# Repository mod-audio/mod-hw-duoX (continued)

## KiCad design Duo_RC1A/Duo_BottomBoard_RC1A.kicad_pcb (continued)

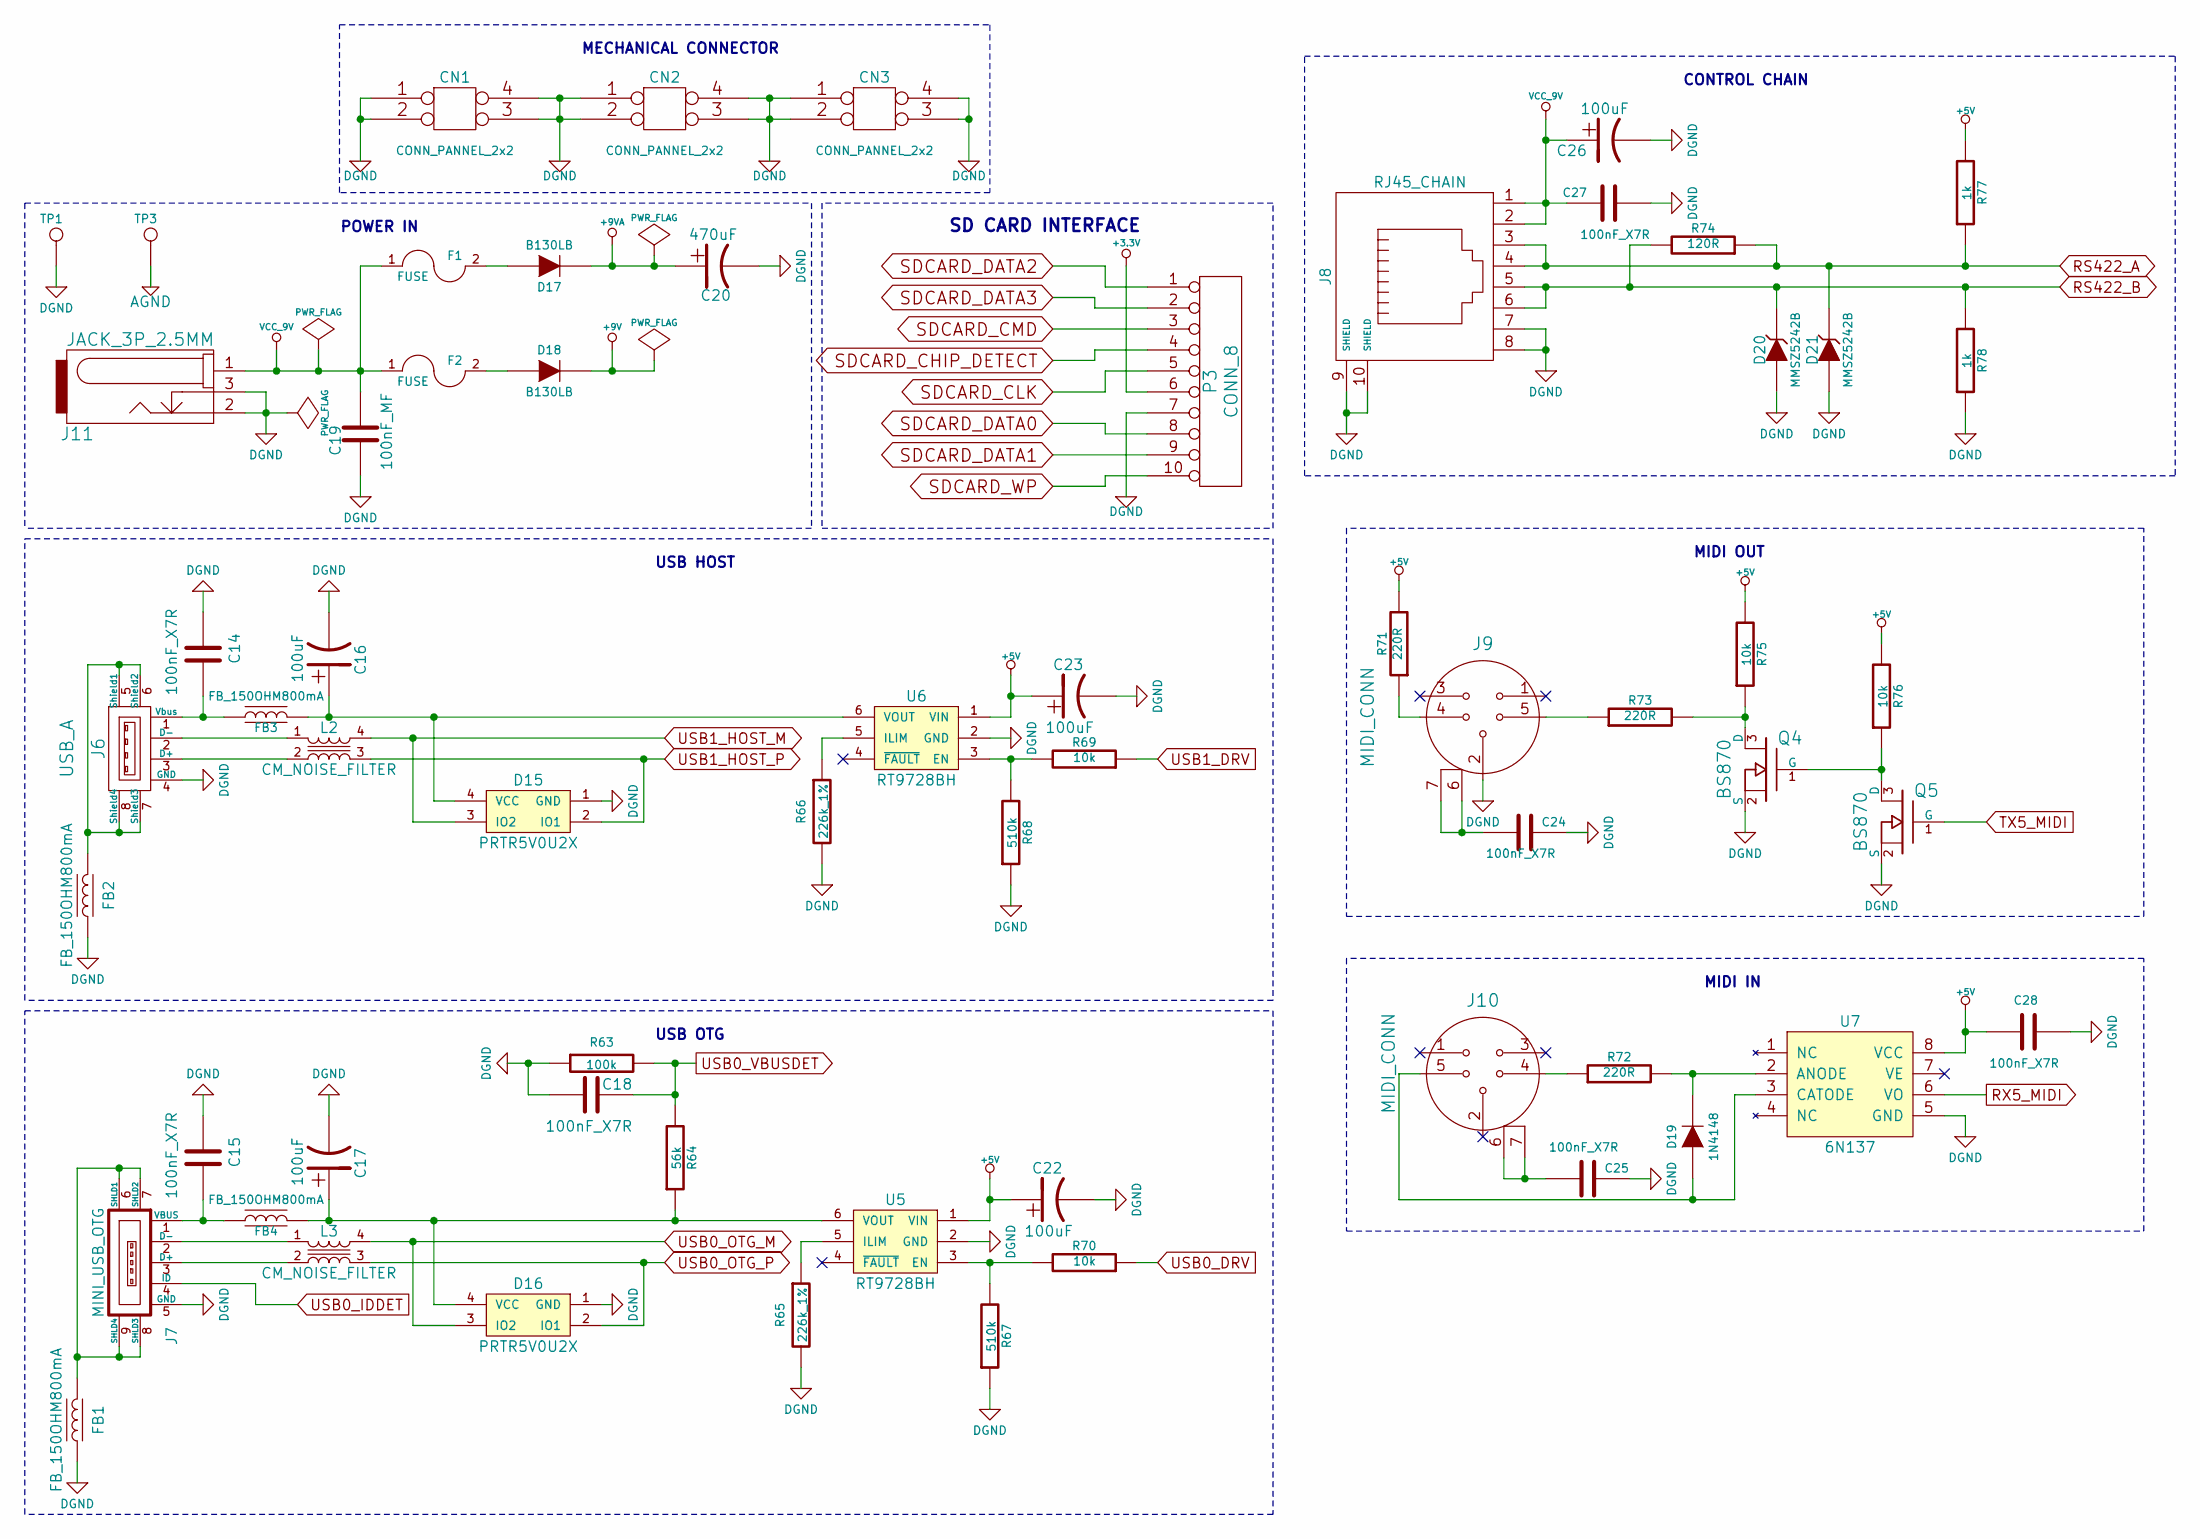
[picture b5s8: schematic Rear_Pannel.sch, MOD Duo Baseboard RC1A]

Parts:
C14, C15, C18, C24, C25, C27, C28: 100nF_X7R; SM0603
C16, C17, C22, C23, C26: 100uF; Capacitor5x11RM2
C19: 100nF_MF; CAP_FILM_12.6X4.5_L10
C20: 470uF; Capacitor8x13RM3.5
CN1, CN2, CN3: CONN_PANNEL_2x2; CONN_PANNEL
D15, D16: PRTR5V0U2X; SOT143B
D17, D18: B130LB; DO-214AA(SMB)
D19: 1N4148; SOD323
D20, D21: MMSZ5242B; SOD123
F1, F2: FUSE; SM2920
FB1, FB2, FB3, FB4: FB_150OHM800mA; SM0805
J6: USB_A; USB_A_73725
J7: MINI_USB_OTG; USB_MINI_B_10033526_N3212LF
J8: RJ45_CHAIN; RJ45_10117863_5036010LF
J9, J10: MIDI_CONN; CON_MIDI_161_0505_E
J11: JACK_3P_2.5MM; PJ-002B
L2, L3: CM_NOISE_FILTER; EXC14CE
P3: CONN_8
Q4, Q5: BS870; SOT23
R63: 100k; SM0603
R64: 56k; SM0603
R65, R66: 226k_1%; SM0603
R67, R68: 510k; SM0603
R69, R70, R75, R76: 10k; SM0603
R71, R72, R73: 220R; SM0805
R74: 120R; SM0805
R77, R78: 1k; SM0603
TP1, TP3: TEST_POINT_2MM; TESTPOINT_2.2MM
U5, U6: RT9728BH; SOT23_6
U7: 6N137; SMD_8

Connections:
+3.3V: P3.6; also elsewhere on the board
+5V: C22.1, C23.1, C28.1, R71.2, R75.2, R76.2, R77.2, U5.1 (VIN), U6.1 (VIN), U7.8 (VCC); also elsewhere on the board
+9V: D18.2 (K); also elsewhere on the board
+9VA: C20.1, D17.2 (K); also elsewhere on the board
DGND: C14.1, C15.1, C16.2, C17.2, C18.1, C19.1, C20.2, C22.2, C23.2, C24.2, C25.2, C26.2, C27.2, C28.2, CN1.1, CN1.2, CN1.3, CN1.4, CN2.1, CN2.2, CN2.3, CN2.4, CN3.1, CN3.2, CN3.3, CN3.4, D15.1 (GND), D16.1 (GND), D20.1 (A), D21.1 (A), FB1.1, FB2.1, J6.4 (GND), J7.5 (GND), J8.7, J8.8, J8.9 (SHIELD), J8.10 (SHIELD), J9.2, J11.2, J11.3, P3.7, Q4.2 (S), Q5.2 (S), R63.1, R65.2, R66.2, R67.1, R68.1, R78.1, TP1.1, TP3.1, U5.2 (GND), U6.2 (GND), U7.5 (GND); also elsewhere on the board
unnamed: C14.2, FB3.1, J6.1 (Vbus)
unnamed: C15.2, FB4.1, J7.1 (VBUS)
unnamed: C16.1, D15.4 (VCC), FB3.2, U6.6 (VOUT)
unnamed: C17.1, D16.4 (VCC), FB4.2, R64.1, U5.6 (VOUT)
unnamed: C24.1, J9.6, J9.7
unnamed: C25.1, J10.6, J10.7
unnamed: D17.1 (A), F1.2
unnamed: D18.1 (A), F2.2
unnamed: D19.1 (A), J10.5, U7.3 (CATODE)
unnamed: D19.2 (K), R72.2, U7.2 (ANODE)
unnamed: FB1.2, J7.6 (SHLD1), J7.7 (SHLD2), J7.8 (SHLD3), J7.9 (SHLD4)
unnamed: FB2.2, J6.5 (Shield1), J6.6 (Shield2), J6.7 (Shield3), J6.8 (Shield4)
unnamed: J6.2 (D-), L2.1
unnamed: J6.3 (D+), L2.2
unnamed: J7.2 (D-), L3.1
unnamed: J7.3 (D+), L3.2
unnamed: J9.4, R71.1
unnamed: J9.5, R73.1
unnamed: J10.4, R72.1
unnamed: Q4.1 (G), Q5.3 (D), R76.1
unnamed: Q4.3 (D), R73.2, R75.1
unnamed: R65.1, U5.5 (ILIM)
unnamed: R66.1, U6.5 (ILIM)
unnamed: R67.2, R70.2, U5.3 (EN)
unnamed: R68.2, R69.2, U6.3 (EN)
RS422_A: D21.2 (K), J8.3, J8.4, R74.1, R77.1; also elsewhere on the board
RS422_B: D20.2 (K), J8.5, J8.6, R74.2, R78.2; also elsewhere on the board
RX5_MIDI: U7.6 (VO); also elsewhere on the board
SDCARD_CHIP_DETECT: P3.4; also elsewhere on the board
SDCARD_CLK: P3.5; also elsewhere on the board
SDCARD_CMD: P3.3; also elsewhere on the board
SDCARD_DATA0: P3.8; also elsewhere on the board
SDCARD_DATA1: P3.9; also elsewhere on the board
SDCARD_DATA2: P3.1; also elsewhere on the board
SDCARD_DATA3: P3.2; also elsewhere on the board
SDCARD_WP: P3.10; also elsewhere on the board
TX5_MIDI: Q5.1 (G); also elsewhere on the board
USB0_DRV: R70.1; also elsewhere on the board
USB0_IDDET: J7.4 (ID); also elsewhere on the board
USB0_OTG_M: D16.3 (IO2), L3.4; also elsewhere on the board
USB0_OTG_P: D16.2 (IO1), L3.3; also elsewhere on the board
USB0_VBUSDET: C18.2, R63.2, R64.2; also elsewhere on the board
USB1_DRV: R69.1; also elsewhere on the board
USB1_HOST_M: D15.3 (IO2), L2.4; also elsewhere on the board
USB1_HOST_P: D15.2 (IO1), L2.3; also elsewhere on the board
VCC_9V: C19.2, C26.1, C27.1, F1.1, F2.1, J8.1, J8.2, J11.1

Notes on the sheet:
MIDI OUT
MIDI IN
CONTROL CHAIN
USB HOST
USB OTG
POWER IN
MECHANICAL CONNECTOR
SD CARD INTERFACE

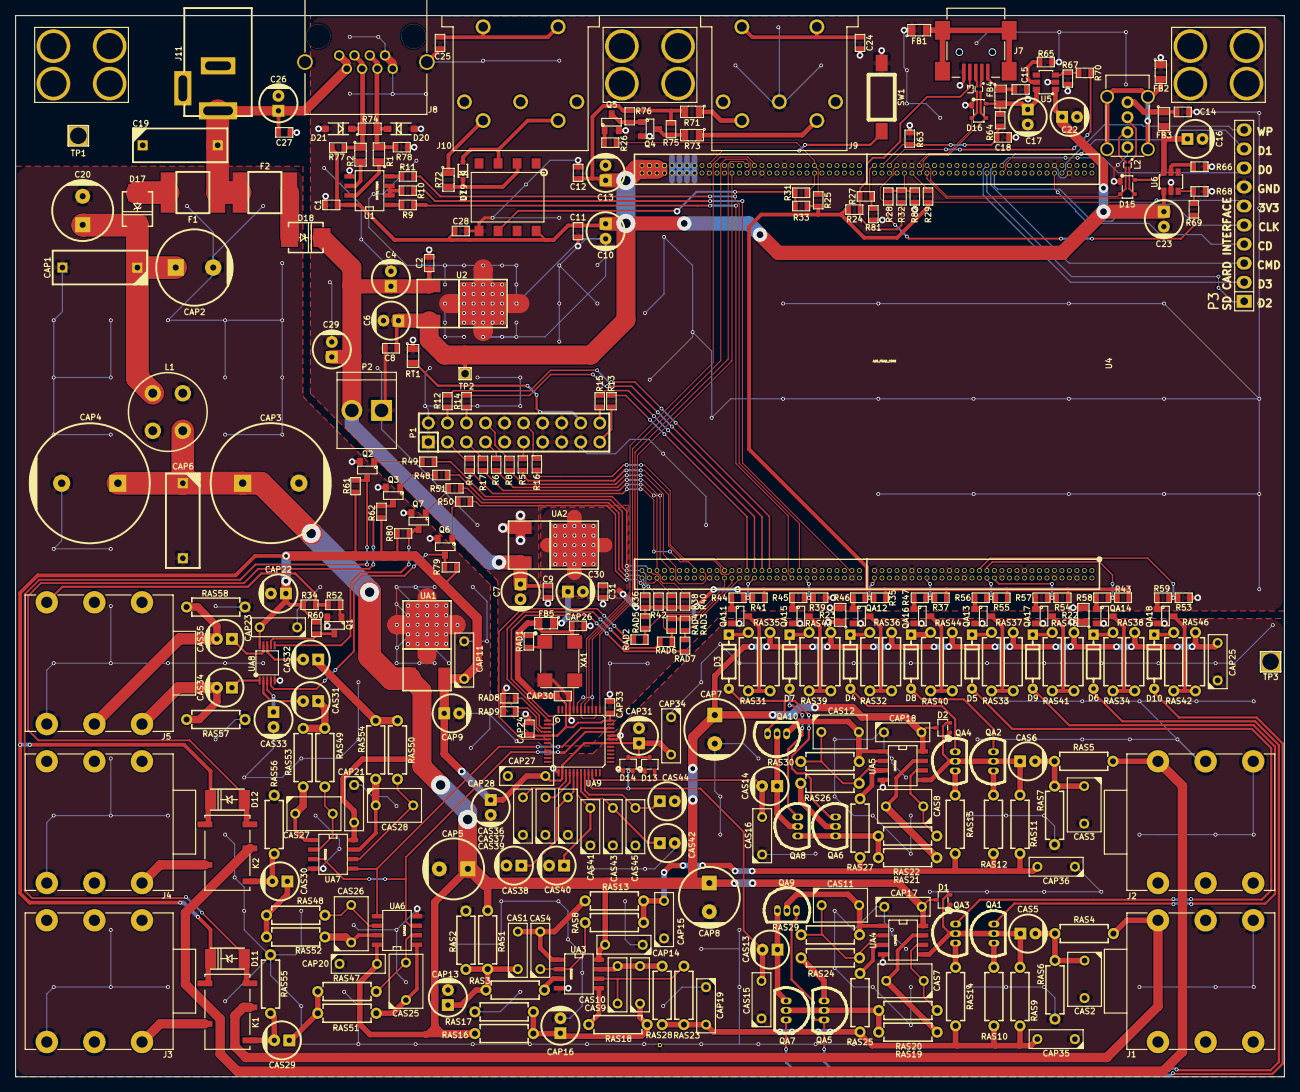
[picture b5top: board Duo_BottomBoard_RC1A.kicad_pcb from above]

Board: 2 copper layers, 169.2 x 141.5 mm, 351 parts (0 on the bottom side), 227 nets.

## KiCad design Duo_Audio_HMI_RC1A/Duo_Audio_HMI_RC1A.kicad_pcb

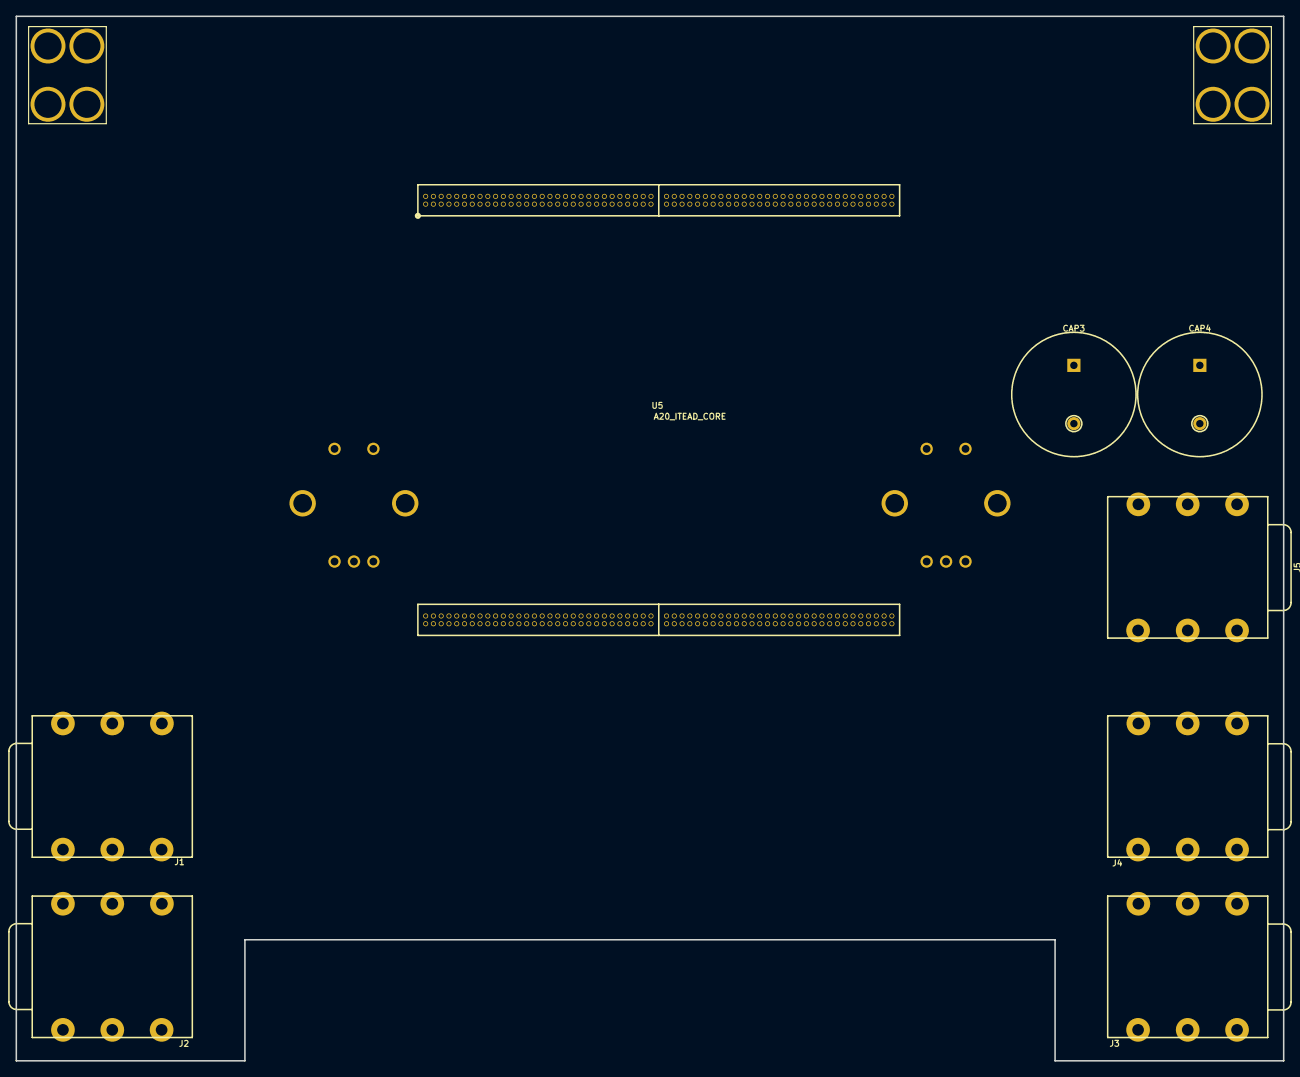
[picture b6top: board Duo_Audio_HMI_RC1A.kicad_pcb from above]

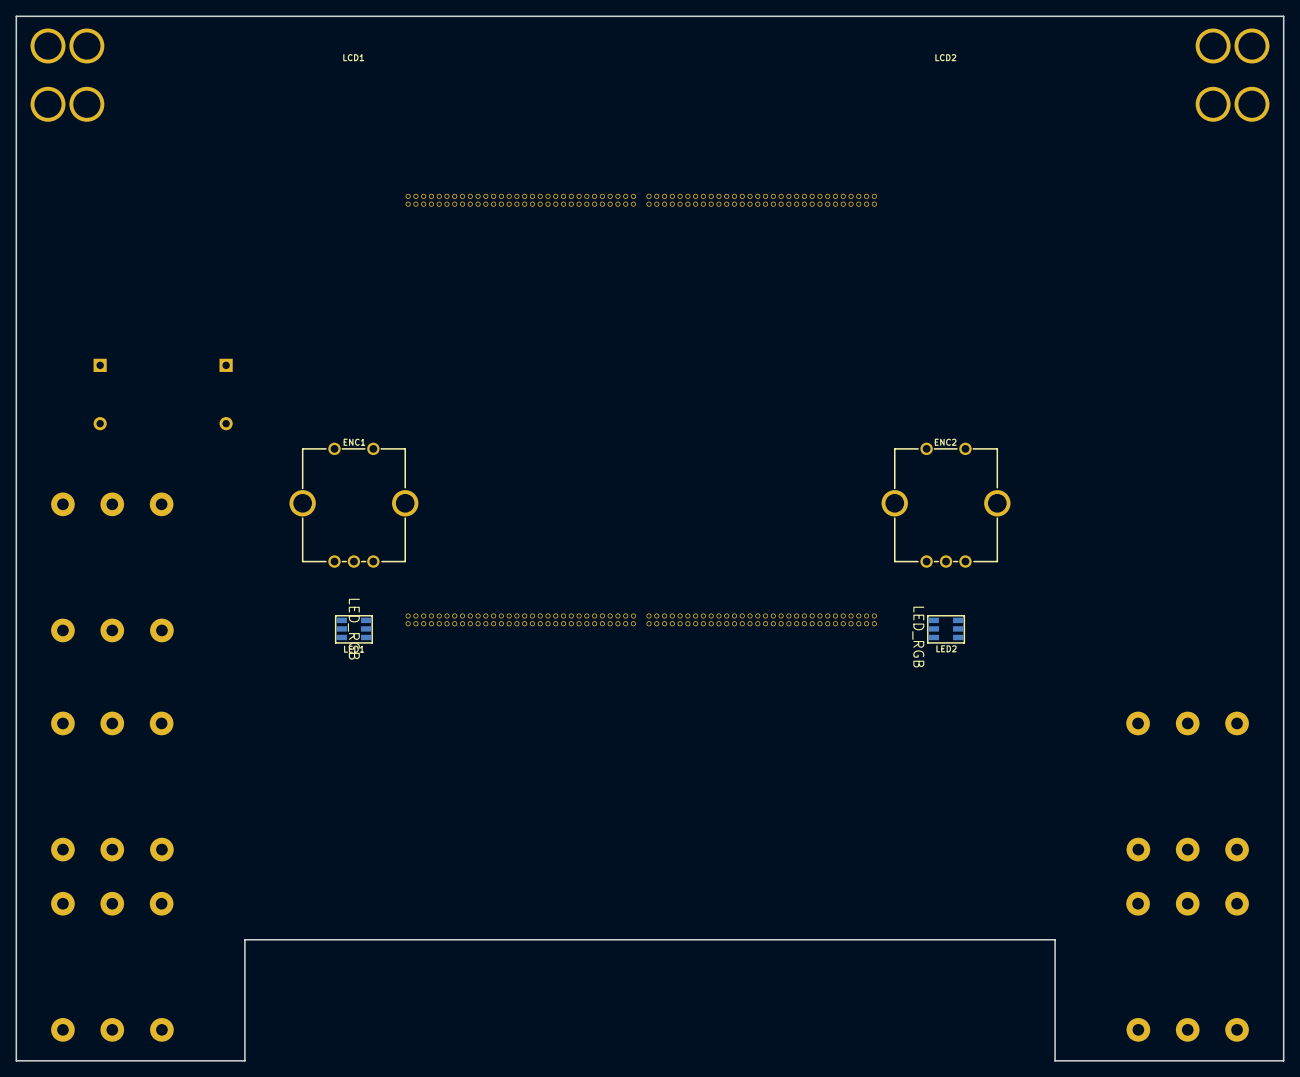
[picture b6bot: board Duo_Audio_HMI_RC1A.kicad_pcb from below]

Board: 2 copper layers, 163.1 x 134.4 mm, 16 parts (6 on the bottom side), 4 nets, no tracks yet.

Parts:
CAP3, CAP4: 4700uF; CAP_RAD_16MM
CN1: PCB_SUPORT
CN2: PCT_SUPORT; PCB_SUPORT
ENC1, ENC2: ENCODER; ENCODER_PEC11_4KS1
J1, J2, J3, J4: JACK_P10_TRS_6P; JACK-NMJ6HCD2_1
J5: JACK_P2_TRS_6P; JACK-NMJ6HCD2_1
LCD1, LCD2: VAL**; LCD_PCB_ERC12864FSF2
LED1, LED2: LED_RGB; LED_CLRTB_GFSF_1
U5: A20_ITEAD_CORE; A20_ITEAD

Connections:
+3.3V: LED1.4, LED1.5, LED1.6, LED2.4, LED2.5, LED2.6
+5V: U5.233, U5.234, U5.235, U5.236, U5.237, U5.238, U5.239, U5.240
AGND: CAP3.2, CAP4.2, ENC1.4, ENC2.4, J1.3, J1.5, J2.3, J2.5, J3.5, J4.3, J4.5, J5.5, U5.6, U5.12, U5.19, U5.26, U5.36, U5.39, U5.49, U5.52, U5.59, U5.64, U5.73, U5.82, U5.92, U5.93, U5.102, U5.104, U5.118, U5.128, U5.131, U5.169, U5.171, U5.201, U5.208, U5.222, U5.225, U5.226, U5.227, U5.228, U5.229, U5.230, U5.231, U5.232
VCC_AMP_AUDIO: CAP3.1, CAP4.1

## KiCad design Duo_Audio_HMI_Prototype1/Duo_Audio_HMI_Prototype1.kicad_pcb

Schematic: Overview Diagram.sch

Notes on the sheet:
CORE BOARD / CPU
ARM Cortex-M3 LPC175x
Audio
I2S
(UART0) SERIAL FIRMWARE x4 (UART1)
(UART2) SERIAL UI x2 (UART2)
HEADER 3x1
RJ45 CHAIN
RS422 CHAIN (UART1)
SPI
GPIO x3 (ANALOG SWITCH)
GPIO x2 (TRUE BYPASS)
(UART3) SERIAL CONSOLE x2 (UART0)
MIDI
SERIAL MIDI x1 (UART3)
DISPLAY1
DISPLAY2
FOOT1
FOOT2
ENCODER1
ENCODER2
HMI
TRANSCIEVER RS422
USB A (HOST)
USB B (DEVICE)

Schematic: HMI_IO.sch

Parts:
C1, C2, C3, C4, C7, C8, C9, C10, C11, C12, C13, C14, C44, C45: 100nF_X7R; SM0603
C5, C6: 100uF; CAP_RAD_5MM
ENC1, ENC2: ENCODER; ENCODER_PEC11_4KS1
FB1, FB2: FB_1kOHM400mA; SM0805
LCD1, LCD2: LCD; LCD-AGM-12864E1-201_1
LED1, LED2: LED_RGB; LED_CLRTB_GFSF_1
P1: HEADER_4X1; PIN_ARRAY_4x1
Q1, Q2: BC847; SOT23
R1, R2, R3, R4, R5, R6, R13, R15, R17, R21, R22, R23, R24, R25, R29, R30: 10k; SM0603
R7, R8, R18, R19, R20, R26, R27, R28: 1k; SM0603
R9, R11: 3k; SM0603
R10, R12: 330R; SM0603
R14, R16: 0R; SM0805
U2, U3, U4, U5: 74HC245; TSSOP20

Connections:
+3.3V: C9.1, C12.1, C44.1, C45.1, FB1.1, FB2.1, LED1.1 (AR), LED1.2 (AG), LED1.3 (AB), LED2.1 (AR), LED2.2 (AG), LED2.3 (AB), R21.1, R23.1, R24.1, R29.1; also elsewhere on the board
+5V: C1.1, C2.1, C3.1, C4.1, C5.1, C6.1, C7.1, C8.1, LCD1.2, LCD1.19, LCD2.2, LCD2.19, R5.1, R6.1, R9.1, R11.1, R13.1, R15.1, U2.20 (VCC), U3.1 (DIR), U3.20 (VCC), U4.20 (VCC), U5.1 (DIR), U5.20 (VCC); also elsewhere on the board
AGND: C1.2, C2.2, C3.2, C4.2, C5.2, C6.2, C7.2, C8.2, C9.2, C10.2, C11.2, C12.2, C13.2, C14.2, C44.2, C45.2, ENC1.4, ENC2.4, LCD1.1, LCD2.1, P1.1, P1.3, Q1.2 (E), Q2.2 (E), R1.1, R2.1, R3.1, R4.1, R17.2, R22.2, R25.2, R30.2, U2.10 (GND), U3.10 (GND), U4.10 (GND), U5.10 (GND); also elsewhere on the board
BACK_LCDA: R7.2; also elsewhere on the board
BACK_LCDB: R8.2; also elsewhere on the board
ENCA_A: C11.1, ENC1.1, R22.1; also elsewhere on the board
ENCA_B: C10.1, ENC1.3, R17.1; also elsewhere on the board
ENCA_BT: ENC1.5, R21.2; also elsewhere on the board
ENCB_A: C14.1, ENC2.1, R30.1; also elsewhere on the board
ENCB_B: C13.1, ENC2.3, R25.1; also elsewhere on the board
ENCB_BT: ENC2.5, R29.2; also elsewhere on the board
FOOT_A: P1.2, R23.2; also elsewhere on the board
FOOT_B: P1.4, R24.2; also elsewhere on the board
LCDA_0: LCD1.7, U2.11 (B8)
LCDA_1: LCD1.8, U2.12 (B7)
LCDA_2: LCD1.9, U2.13 (B6)
LCDA_3: LCD1.10, U2.14 (B5)
LCDA_4: LCD1.11, U2.15 (B4)
LCDA_5: LCD1.12, U2.16 (B3)
LCDA_6: LCD1.13, U2.17 (B2)
LCDA_7: LCD1.14, U2.18 (B1)
LCDA_CS1: LCD1.15, R1.2, U3.17 (B2)
LCDA_CS2: LCD1.16, R3.2, U3.18 (B1)
LCDA_EN: LCD1.6, U3.15 (B4)
LCDA_RS: LCD1.4, U3.13 (B6)
LCDA_RST: LCD1.17, R5.2, U3.16 (B3)
LCDA_RW: LCD1.5, U3.14 (B5)
LCDB_0: LCD2.7, U4.11 (B8)
LCDB_1: LCD2.8, U4.12 (B7)
LCDB_2: LCD2.9, U4.13 (B6)
LCDB_3: LCD2.10, U4.14 (B5)
LCDB_4: LCD2.11, U4.15 (B4)
LCDB_5: LCD2.12, U4.16 (B3)
LCDB_6: LCD2.13, U4.17 (B2)
LCDB_7: LCD2.14, U4.18 (B1)
LCDB_CS1: LCD2.15, R2.2, U5.17 (B2)
LCDB_CS2: LCD2.16, R4.2, U5.18 (B1)
LCDB_EN: LCD2.6, U5.15 (B4)
LCDB_RS: LCD2.4, U5.13 (B6)
LCDB_RST: LCD2.17, R6.2, U5.16 (B3)
LCDB_RW: LCD2.5, U5.14 (B5)
LCD_0: U2.9 (A8), U4.9 (A8); also elsewhere on the board
LCD_1: U2.8 (A7), U4.8 (A7); also elsewhere on the board
LCD_2: U2.7 (A6), U4.7 (A6); also elsewhere on the board
LCD_3: U2.6 (A5), U4.6 (A5); also elsewhere on the board
LCD_4: U2.5 (A4), U4.5 (A4); also elsewhere on the board
LCD_5: U2.4 (A3), U4.4 (A3); also elsewhere on the board
LCD_6: U2.3 (A2), U4.3 (A2); also elsewhere on the board
LCD_7: U2.2 (A1), U4.2 (A1); also elsewhere on the board
LCD_CS1: U3.3 (A2), U5.3 (A2); also elsewhere on the board
LCD_CS2: U3.2 (A1), U5.2 (A1); also elsewhere on the board
LCD_DIR: U2.1 (DIR), U4.1 (DIR); also elsewhere on the board
LCD_EN: U3.5 (A4), U5.5 (A4); also elsewhere on the board
LCD_RS: U3.7 (A6), U5.7 (A6); also elsewhere on the board
LCD_RST: U3.4 (A3), U5.4 (A3); also elsewhere on the board
LCD_RW: U3.6 (A5), U5.6 (A5); also elsewhere on the board
LEDA_B: R20.2; also elsewhere on the board
LEDA_G: R19.2; also elsewhere on the board
LEDA_R: R18.2; also elsewhere on the board
LEDB_B: R28.2; also elsewhere on the board
LEDB_G: R27.2; also elsewhere on the board
LEDB_R: R26.2; also elsewhere on the board
unnamed: LCD1.18, R10.1
unnamed: Q1.1 (B), R7.1
unnamed: ENC2.2, FB2.2
unnamed: ENC1.2, FB1.2
unnamed: Q2.1 (B), R8.1
unnamed: LCD1.3, R9.2, R10.2
unnamed: LCD2.3, R11.2, R12.2
unnamed: LCD1.20, R14.1
unnamed: Q1.3 (C), R13.2, R14.2
unnamed: LCD2.18, R12.1
unnamed: LCD2.20, R16.1
unnamed: Q2.3 (C), R15.2, R16.2
unnamed: LED1.6 (KR), R18.1
unnamed: LED1.5 (KG), R19.1
unnamed: LED1.4 (KB), R20.1
unnamed: LED2.4 (KB), R28.1
unnamed: LED2.6 (KR), R26.1
unnamed: LED2.5 (KG), R27.1
S_LCDA: U2.19 (~OE), U3.19 (~OE); also elsewhere on the board
S_LCDB: U4.19 (~OE), U5.19 (~OE); also elsewhere on the board

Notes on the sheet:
CURRENT FOR LCD: 5mA CURRENT FOR BACKLIGHT: 14mA
LCD1
LCD2
LED RGB 1/2
ENCODER 1
ENCODER 2
FOOT 1/2

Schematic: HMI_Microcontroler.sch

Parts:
C15, C16, C17, C18, C19, C20, C21, C22, C25: 100nF_X7R; SM0603
C23, C24: 18pF_NP0; SM0603
FB3: FB_1kOHM400mA; SM0805
LED3: LED_SMD; SM0805
P2: HEADER_10X2; PIN_ARRAY_2X10
R31, R48: 1k; SM0603
R32, R33, R35, R36, R37, R38, R39, R40, R41, R42, R43, R44, R45, R46, R47, R49, R50, R65, R66, R67: 10k; SM0603
R34: 0R; SM0805
RT1: NTC; SM0805
SW1: SW_TACTILE_6X6_4PIN; TACTILE_SWITCH_6x6
U1: LPC175XFBD80; LQFP80
U6: TLV803; SOT23
U7: 74LVC1G125; SOT353
X1: 10MHz; HC_49US

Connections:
+3.3V: C15.1, C16.1, C17.1, C18.1, C19.1, C22.1, C25.1, FB3.1, R31.2, R32.1, R33.1, R34.1, R35.1, R36.1, R37.1, R38.1, R40.1, R42.1, R44.1, R46.1, R47.1, R48.1, R49.1, R50.1, R65.1, R66.1, R67.1, U1.16 (VBAT), U1.21 (VDD(3V3)), U1.34 (VDD(REG)(3V3)), U1.42 (VDD(3V3)), U1.56 (VDD(3V3)), U1.67 (VDD(REG)(3V3)), U1.77 (VDD(3V3)), U6.3 (VDD), U7.5 (VCC); also elsewhere on the board
AGND: C15.2, C16.2, C17.2, C18.2, C19.2, C20.2, C21.2, C22.2, C23.2, C24.2, C25.2, P2.4, P2.6, P2.8, P2.10, P2.12, P2.14, P2.16, P2.18, P2.20, R39.1, R41.1, R43.1, R45.1, RT1.2, SW1.3, SW1.4, U1.9 (VSSA), U1.12 (VREFN), U1.24 (VSS), U1.33 (VSS), U1.43 (VSS), U1.57 (VSS), U1.66 (VSS), U1.78 (VSS), U6.1 (GND), U7.2 (A), U7.3 (GND); also elsewhere on the board
BACK_LCDA: R32.2, U1.32 (P1[26]/MCOB1/PWM1[6]/CAP0[0]); also elsewhere on the board
BACK_LCDB: R33.2, U1.31 (P1[25]/MCOA1/MAT1[1]); also elsewhere on the board
ENCA_A: U1.28 (P1[22]/MCOB0/USB_PWRD/MAT1[0]); also elsewhere on the board
ENCA_B: U1.29 (P1[23]/MCI1/PWM1[4]/MISO0); also elsewhere on the board
ENCA_BT: U1.30 (P1[24]/MCI2/PWM1[5]/MOSI0); also elsewhere on the board
ENCB_A: U1.62 (P0[8]/I2STX_WS/MISO1/MAT2[2]); also elsewhere on the board
ENCB_B: U1.63 (P0[7]/I2STX_CLK/SCK1/MAT2[1]); also elsewhere on the board
ENCB_BT: U1.64 (P0[6]/I2SRX_SDA/SSEL1/MAT2[0]); also elsewhere on the board
FOOT_A: U1.22 (P0[29]/USB_D+); also elsewhere on the board
FOOT_B: U1.23 (P0[30]/USB_D-); also elsewhere on the board
LCD_0: U1.60 (P2[0]/PWM1[1]/TXD1); also elsewhere on the board
LCD_1: U1.59 (P2[1]/PWM1[2]/RXD1); also elsewhere on the board
LCD_2: U1.58 (P2[2]/PWM1[3]/CTS1/TRACEDATA[3]); also elsewhere on the board
LCD_3: U1.55 (P2[3]/PWM1[4]/DCD1/TRACEDATA[2]); also elsewhere on the board
LCD_4: U1.54 (P2[4]/PWM1[5]/DSR1/TRACEDATA[1]); also elsewhere on the board
LCD_5: U1.53 (P2[5]/PWM1[6]/DTR1/TRACEDATA[0]); also elsewhere on the board
LCD_6: U1.52 (P2[6]/PCAP1[0]/RI1/TRACECLK); also elsewhere on the board
LCD_7: U1.51 (P2[7]/RD2/RTS1); also elsewhere on the board
LCD_CS1: U1.39 (P0[10]/TXD2/SDA2/MAT3[0]); also elsewhere on the board
LCD_CS2: U1.40 (P0[11]/RXD2/SCL2/MAT3[1]); also elsewhere on the board
LCD_DIR: U1.46 (P0[17]/CTS1/MISO0/MISO); also elsewhere on the board
LCD_EN: U1.37 (P0[0]/RD1/TXD3/SDA1); also elsewhere on the board
LCD_RS: U1.35 (P1[28]/MCOA2/PCAP1[0]/MAT0[0]); also elsewhere on the board
LCD_RST: U1.38 (P0[1]/TD1/RXD3/SCL1); also elsewhere on the board
LCD_RW: U1.36 (P1[29]/MCOB2/PCAP1[1]/MAT0[1]); also elsewhere on the board
LEDA_B: U1.18 (P1[30]/VBUS/AD0[4]); also elsewhere on the board
LEDA_G: U1.17 (P1[31]/SCK1/AD0[5]); also elsewhere on the board
LEDA_R: U1.6 (P0[26]/AD0[3]/AOUT/RXD3); also elsewhere on the board
LEDB_B: U1.25 (P1[18]/USB_UP_LED/PWM1[1]/CAP1[0]); also elsewhere on the board
LEDB_G: U1.26 (P1[19]/MCOA0/~USB_PPWR~/CAP1[1]); also elsewhere on the board
LEDB_R: U1.27 (P1[20]/MCI0/PWM1[2]/SCK0); also elsewhere on the board
unnamed: LED3.1 (A), R31.1
unnamed: LED3.2 (K), U1.65 (P4[28]/RX_MCLK/MAT2[0]/TXD3)
unnamed: R35.2, U1.41 (P2[10]/~EINT0~/NMI)
unnamed: C21.1, FB3.2, U1.8 (VDDA), U1.10 (VREFP)
unnamed: C23.1, U1.19 (XTAL1), X1.2
unnamed: C24.1, U1.20 (XTAL2), X1.1
unnamed: P2.11, R41.2
unnamed: P2.1, P2.2, R34.2
unnamed: P2.17, R43.2
unnamed: P2.19, R45.2
NTC_TEMP: C20.1, R49.2, RT1.1, U1.7 (P0[25]/AD0[2]/I2SRX_SDA/TXD3)
OE_UC_CHAIN: R66.2, U1.44 (P0[22]/RTS1/TD1); also elsewhere on the board
RESET: P2.15, R50.2, U1.14 (~RESET), U7.4 (Y)
RESET_UC_CTL: R48.2, SW1.1, SW1.2, U6.2 (~RESET), U7.1 (~OE); also elsewhere on the board
RESET_UC_EN: U1.72 (P1[9]/ENET_RXD0); also elsewhere on the board
RX1_UC_CHAIN: R65.2, U1.48 (P0[16]/RXD1/SSEL0/SSEL); also elsewhere on the board
RXD0_HMI_CONSOLE: R37.2, U1.80 (P0[3]/RXD0/AD0[6]); also elsewhere on the board
RXD2_HMI_UI: R47.2, U1.49 (P2[9]/USB_CONNECT/RXD2); also elsewhere on the board
S_LCDA: U1.45 (P0[18]/DCD1/MOSI0/MOSI); also elsewhere on the board
S_LCDB: U1.61 (P0[9]/I2STX_SDA/MOSI1/MAT2[3]); also elsewhere on the board
TCK_SWDCLK: P2.9, R39.2, U1.5 (TCK/SWDCLK)
TDI: P2.5, R40.2, U1.2 (TDI)
TDO_SWO: P2.13, R44.2, U1.1 (TDO/SWO)
TMS_SDWIO: P2.7, R42.2, U1.3 (TMS/SWDIO)
TX1_UC_CHAIN: R67.2, U1.47 (P0[15]/TXD1/SCK0/SCK); also elsewhere on the board
TXD0_HMI_CONSOLE: R36.2, U1.79 (P0[2]/TXD0/AD0[7]); also elsewhere on the board
TXD2_HMI_UI: R46.2, U1.50 (P2[8]/TD2/TXD2); also elsewhere on the board
~TRST: P2.3, R38.2, U1.4 (~TRST)

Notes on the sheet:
uC JTAG/SWD
uC RESET
uC CRYSTAL
uC POWER
uC I/O
uC TEST LED
NTC

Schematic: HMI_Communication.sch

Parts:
C26: 100nF_X7R; SM0603
D1: 1N4148; SOD323
JP1: HEADER_4X2; PIN_ARRAY_4X2
Q3: BC847; SOT23
R51, R52, R53, R54, R55, R56, R57: 100R; SM0603
R58, R59: 0R; SM0805
R60, R61: 10R; SM0805
R63: 10k; SM0603
R64: 33k; SM0603
U8: ISL83485; SO8E

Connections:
+3.3V: JP1.3, JP1.4, R59.1; also elsewhere on the board
+5V: R58.1; also elsewhere on the board
AGND: C26.1, D1.1 (A), JP1.1, JP1.2, Q3.2 (E), R63.1, U8.5 (GND); also elsewhere on the board
unnamed: R53.2, U8.4 (D)
unnamed: JP1.8, R54.1
unnamed: C26.2, R58.2, R59.2, U8.8 (VCC)
unnamed: R51.2, U8.1 (R)
unnamed: R61.2, U8.6 (A)
unnamed: R60.1, U8.7 (B)
unnamed: R52.2, U8.2 (~RE), U8.3 (DE)
unnamed: JP1.6, R55.2
OE_UC_CHAIN: R52.1; also elsewhere on the board
RESET_UC_CTL: Q3.3 (C); also elsewhere on the board
RESET_UC_CTL_HOST: R64.1; also elsewhere on the board
RESET_UC_EN: D1.2 (K), Q3.1 (B), R63.2, R64.2; also elsewhere on the board
RS422_A: R61.1; also elsewhere on the board
RS422_B: R60.2; also elsewhere on the board
RX1_UC_CHAIN: R51.1; also elsewhere on the board
RX5_HOST_UI: R56.2; also elsewhere on the board
RX6_HOST_CONSOLE: R54.2; also elsewhere on the board
RXD0_HMI_CONSOLE: JP1.5; also elsewhere on the board
RXD2_HMI_UI: R57.2; also elsewhere on the board
TX1_UC_CHAIN: R53.1; also elsewhere on the board
TX5_HOST_UI: R57.1; also elsewhere on the board
TX6_HOST_CONSOLE: R55.1; also elsewhere on the board
TXD0_HMI_CONSOLE: JP1.7; also elsewhere on the board
TXD2_HMI_UI: R56.1; also elsewhere on the board

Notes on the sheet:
RS422
SERIAL UI
SERIAL CONSOLE
MICROCONTROLLER RESET CONTROL

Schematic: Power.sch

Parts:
C27: 1000uF; CAP_RAD_10MM
C28, C29, C31: 100nF_MKP; CAP_FILM_18X5_L15
C30: 470uF; CAP_RAD_8MM
C32, C33: 100uF; CAP_RAD_5MM
C34, C35: 100nF_X7R; SM0603
C46, C47: 100nF_MF; CAP_FILM_12.6X4.5_L10
CAP1, CAP2, CAP4, CAP15, CAP16: 470uF; CAP_RAD_8MM
CAP3: 100nF; SM0603
CAP18: 100nF_MF; CAP_FILM_12.6X4.5_L10
CAP19, CAP20: 4.7mF; CAP_RAD_16MM
D3: B130LB; DO-214AA(SMB)
F1: PTC_2A; SM2920
L1: 220uH_1.1A_290mR; IND_RAD_10MM_4P
L2: 500mH_50mA; IND_RAD_10MM_4P
P3: KK3.96_2PIN
R69, R70, R71: 0R; SM0805
TP1, TP2, TP3, TP4, TP5: CONN_1; SIL-1
U9: MC78M05; DPAK(369C)
U10: MC7805; DPAK(369C)
U11: NCP1117DT33G; DPAK(369C)

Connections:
+3.3V: L2.1, L2.2, R71.2; also elsewhere on the board
+5V: R70.2; also elsewhere on the board
+5VA: CAP16.1, R69.2; also elsewhere on the board
+9V: F1.1, P3.1
AGND: C27.2, C28.2, C29.2, C30.2, C31.2, C32.2, C33.2, C34.2, C35.2, C46.2, C47.2, CAP1.2, CAP2.2, CAP3.2, CAP4.2, CAP15.2, CAP16.2, CAP18.2, CAP19.2, CAP20.2, L1.2, L1.4, P3.2 (PM), TP1.1, U9.2 (GND), U10.2 (GND), U11.1 (GND); also elsewhere on the board
unnamed: C33.1, C35.1, R71.1, TP4.1, U11.2 (VOUT)
unnamed: D3.1 (A), F1.2
unnamed: CAP2.1, CAP3.1, R69.1, TP3.1, U9.3 (VOUT)
unnamed: C32.1, C34.1, R70.1, TP5.1, U10.3 (VOUT)
VCC: C27.1, C29.1, C30.1, C31.1, C46.1, C47.1, D3.2 (K), L1.1, TP2.1, U10.1 (VIN), U11.3 (VIN)
VCC_AMP_AUDIO: C28.1, CAP1.1, CAP4.1, CAP15.1, CAP18.1, CAP19.1, CAP20.1, L1.3, U9.1 (VIN); also elsewhere on the board

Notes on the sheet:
HMI POWER
AUDIO POWER
CURRENT SUPPLY LCDs: 40mA USB HOST: 150mA TOTAL:
5V 500mA
5V 1A
3.3V 1A

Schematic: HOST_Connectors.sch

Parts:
C36, C39, C40, C43: 100uF; CAP_RAD_5MM
C37, C38, C41, C42: 100nF_X7R; SM0603
CAP17: 100nF; SM0603
D9, D10: BAT854SW; SOT323
GND1, GND3, GND4, GND5, GND6, GND7, GND8, GND9, GND11, GND12, GND13, GND14, GND15, GND16: CONN_1; PAD_GND
JP2: HEADER_3X2; PIN_ARRAY_3X2
JP3: HEADER_4X2; PIN_ARRAY_4X2
P4: HEADER_8X2; pin_array_8x2
R62, R68: 100R; SM0805
R72: 100R; RES_PTH_6MM
R77, R78, R79, R80, R81, R82, R83, R84: 1k; SM0603
U12: CUBIEBOARD2

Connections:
+3.3V: C40.1, C41.1, P4.3; also elsewhere on the board
+5V: C36.1, C37.1, C38.2, C39.1, C42.1, C43.1, P4.4, U12.A_43 (VCC_5V), U12.B_1 (VCC_5V); also elsewhere on the board
AGND: C36.2, C37.2, C38.1, C39.2, C40.2, C41.2, C42.2, C43.2, CAP17.2, D9.1 (Anode), D10.1 (Anode), GND1.1, GND3.1, GND4.1, GND5.1, GND6.1, GND7.1, GND8.1, GND9.1, GND11.1, GND12.1, GND13.1, GND14.1, GND15.1, GND16.1, JP2.1, JP2.2, P4.1, P4.2, U12.A_2 (GND), U12.A_9 (GND), U12.A_20 (GND), U12.A_38 (GND), U12.A_42 (GND), U12.B_19 (GND), U12.B_20 (GND), U12.B_25 (GND), U12.B_37 (GND); also elsewhere on the board
AMPOUT_L_IN: JP3.2; also elsewhere on the board
AMPOUT_L_OUT: JP3.5; also elsewhere on the board
AMPOUT_R_IN: JP3.1; also elsewhere on the board
AMPOUT_R_OUT: JP3.3; also elsewhere on the board
AVCC_CUBIE: R72.2, U12.B_39 (AVCC)
BUFF_L_SW: R78.2; also elsewhere on the board
BYPASS_L_EN: U12.B_2 (PH15); also elsewhere on the board
BYPASS_R_EN: U12.B_4 (PH14); also elsewhere on the board
FMIN_L: JP2.6, U12.B_21 (FMINL)
FMIN_R: JP2.4, U12.B_23 (FMINR)
HPL_CUBIE: JP3.4, U12.B_45 (HPL)
HPR_CUBIE: JP3.6, U12.B_47 (HPR)
IN_L_SW: D9.3 (AK), JP2.5; also elsewhere on the board
IN_R_SW: D10.3 (AK), JP2.3; also elsewhere on the board
JFET_SW_R1: R84.2; also elsewhere on the board
JFET_SW_R2: R83.2; also elsewhere on the board
JFET_SW_R3: R82.2; also elsewhere on the board
JFET_SW_R4: R81.2; also elsewhere on the board
LINE_L_Z_SW: R79.2; also elsewhere on the board
MIC_L_GAIN_SW: R77.2; also elsewhere on the board
MIC_L_Z_SW: R80.2; also elsewhere on the board
unnamed: P4.13, R68.2
unnamed: P4.15, R62.2
unnamed: R81.1, U12.B_42 (PE8)
unnamed: R82.1, U12.B_44 (PE9)
unnamed: R83.1, U12.B_46 (PE10)
unnamed: R84.1, U12.B_48 (PE11)
unnamed: R77.1, U12.B_34 (PE4)
unnamed: R78.1, U12.B_36 (PE5)
unnamed: R79.1, U12.B_38 (PE6)
unnamed: R80.1, U12.B_40 (PE7)
unnamed: CAP17.1, D9.2 (cathode), D10.2 (cathode), R72.1
OUT_L: JP3.8; also elsewhere on the board
OUT_R: JP3.7; also elsewhere on the board
RESET_UC_CTL_HOST: U12.A_4 (PD1); also elsewhere on the board
RS422_A: P4.14; also elsewhere on the board
RS422_B: P4.16; also elsewhere on the board
RX4_HOST_MIDI: R62.1, U12.B_18 (PG11)
RX5_HOST_UI: U12.A_47 (PI11); also elsewhere on the board
RX6_HOST_CONSOLE: U12.A_48 (PI13); also elsewhere on the board
TX4_HOST_MIDI: R68.1, U12.B_17 (PG10)
TX5_HOST_UI: U12.A_45 (PI10); also elsewhere on the board
TX6_HOST_CONSOLE: U12.A_46 (PI12); also elsewhere on the board

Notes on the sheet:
CORE BOARD CUBIEBOARD2
REAR PANNEL CONNECTOR
AUDIO SIGNAL

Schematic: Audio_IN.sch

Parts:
CAP5, CAP8: 10uF; CAP_RAD_5MM
CAP6, CAP7, CAP9, CAP10, CAP11, CAP12, CAP13: 100nF; SM0603
CAS1, CAS4, CAS9, CAS10, CAS11, CAS12: 100nF; SM0603
CAS2, CAS5: 10nF; SM0603
CAS3, CAS7, CAS13, CAS15: 10uF; CAP_RAD_5MM
CAS6, CAS14: 200pF; SM0603
CAS8, CAS16: 2.2nF; SM0603
D2, D6, D7, D8: 1N4447; DO-35
GNDA1, GNDA2, GNDA3, GNDA4, GNDA5, GNDA6, GNDA7, GNDA8, GNDA9, GNDA10, GNDA11, GNDA12, GNDA13, GNDA14, GNDA15, GNDA16, GNDA17, GNDA18, GNDA19, GNDA20: CONN_1; PAD_GND
J3, J4: JACK_P10_TRS_6P; JACK-NMJ6HCD2_1
Q4, Q7, Q8, Q9, Q10, Q11, Q12, Q13: BS870; SOT23
QA1, QA2, QA3, QA4, QA5: J113; TO92_
RAS1, RAS2, RAS6, RAS12, RAS13, RAS17: 50k; RES_PTH_6MM
RAS3, RAS15: 25k; RES_PTH_6MM
RAS4, RAS20, RAS24, RAS40: 100R; RES_PTH_6MM
RAS5, RAS7, RAS23, RAS42: 1M; RES_PTH_6MM
RAS8, RAS14, RAS16, RAS25, RAS26, RAS27, RAS28, RAS29, RAS30, RAS31, RAS32, RAS34: 10k; RES_PTH_6MM
RAS9, RAS35, RAS36, RAS41: 10k; SM0603
RAS10, RAS21: 50R; RES_PTH_6MM
RAS11, RAS33: 3k; RES_PTH_6MM
RAS18, RAS19, RAS37, RAS38: 500R; RES_PTH_6MM
RAS22, RAS39: 15k; RES_PTH_6MM
TP6, TP7: CONN_1; SIL-1
UA1, UA2, UA4: LM4562; SO8E
UA3, UA5: 74LVC4066; SO14E

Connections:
+5VA: CAP11.2, CAP12.2, CAP13.2, RAS9.2, RAS12.1, RAS35.2, RAS36.2, RAS41.2, UA3.14 (VCC), UA4.8 (V+), UA5.14 (VCC); also elsewhere on the board
AGND: CAP5.2, CAP6.1, CAP7.1, CAP8.2, CAP9.1, CAP10.1, CAP11.1, CAP12.1, CAP13.1, CAS8.1, CAS9.2, CAS10.2, CAS11.2, CAS12.2, CAS16.1, GNDA1.1, GNDA2.1, GNDA3.1, GNDA4.1, GNDA5.1, GNDA6.1, GNDA7.1, GNDA8.1, GNDA9.1, GNDA10.1, GNDA11.1, GNDA12.1, GNDA13.1, GNDA14.1, GNDA15.1, GNDA16.1, GNDA17.1, GNDA18.1, GNDA19.1, GNDA20.1, J3.3, J3.5, J4.3, J4.5, Q4.2 (S), Q7.2 (S), Q8.2 (S), Q9.2 (S), Q10.2 (S), Q11.2 (S), Q12.2 (S), Q13.2 (S), RAS2.2, RAS5.2, RAS13.2, RAS23.2, UA1.4 (V-), UA2.4 (V-), UA3.7 (GND), UA4.4 (V-), UA5.7 (GND); also elsewhere on the board
BIAS_AMP_LEFT: CAP10.2, RAS14.2, RAS21.1, RAS33.1, RAS38.2, RAS42.1, TP7.1
BIAS_AMP_RIGHT: CAP7.2, RAS7.1, RAS8.1, RAS10.1, RAS11.1, RAS19.2, TP6.1
BUFF_L_OUT: RAS34.2, UA4.1, UA5.2 (1Z), UA5.3 (2Z), UA5.10 (4Z)
BUFF_L_SW: Q12.1 (G); also elsewhere on the board
IN_L: J4.1, RAS20.2; also elsewhere on the board
IN_L_SW: CAS15.1, CAS16.2; also elsewhere on the board
IN_L_SW_CMOS: RAS40.2, UA5.1 (1Y), UA5.9 (3Z), UA5.11 (4Y)
IN_R: J3.1, RAS4.2; also elsewhere on the board
IN_R_SW: CAS7.1, CAS8.2; also elsewhere on the board
JFET_SW_R1: Q4.1 (G); also elsewhere on the board
JFET_SW_R2: Q7.1 (G); also elsewhere on the board
JFET_SW_R3: Q8.1 (G); also elsewhere on the board
JFET_SW_R4: Q9.1 (G); also elsewhere on the board
LINE_L_Z: CAS13.1, RAS42.2, UA3.1 (1Y), UA3.4 (2Y), UA3.9 (3Z), UA3.10 (4Z), UA4.3 (+)
LINE_L_Z_SW: Q10.1 (G); also elsewhere on the board
MIC_L_GAIN_IN: RAS37.2, UA5.4 (2Y)
MIC_L_GAIN_OUT: CAS14.2, RAS39.1, UA4.7, UA5.8 (3Y)
MIC_L_GAIN_SW: Q13.1 (G); also elsewhere on the board
MIC_L_Z_SW: Q11.1 (G); also elsewhere on the board
unnamed: QA4.1 (D), QA5.2 (S), RAS24.2
unnamed: QA2.2 (S), RAS11.2
unnamed: QA1.2 (S), RAS8.2
unnamed: CAS13.2, RAS20.1, RAS23.1
unnamed: QA3.1 (D), RAS18.2
unnamed: Q9.3 (D), RAS28.2, RAS32.2
unnamed: CAS15.2, RAS40.1
unnamed: RAS14.1, UA3.2 (1Z), UA3.3 (2Z)
unnamed: RAS34.1, UA4.2 (-)
unnamed: RAS38.1, UA4.5 (+)
unnamed: CAS14.1, RAS37.1, RAS39.2, UA4.6 (-)
unnamed: CAS5.1, RAS17.2, UA2.6 (-)
unnamed: CAS3.2, RAS4.1, RAS5.1
unnamed: CAS3.1, QA1.1 (D), QA2.1 (D), RAS7.2, UA1.3 (+)
unnamed: RAS16.1, UA1.2 (-)
unnamed: CAP8.1, CAS4.1, RAS12.2, RAS13.1, RAS15.1
unnamed: RAS15.2, UA2.5 (+)
unnamed: CAS4.2, CAS5.2, RAS17.1, RAS21.2, UA2.7
unnamed: CAS7.2, RAS24.1
unnamed: Q4.3 (D), RAS25.2, RAS29.2
unnamed: Q8.3 (D), RAS27.2, RAS31.2
unnamed: CAS6.2, QA5.1 (D), RAS22.1, UA1.7
unnamed: QA3.2 (S), QA4.2 (S), RAS16.2, UA1.1
unnamed: RAS19.1, UA1.5 (+)
unnamed: CAS6.1, RAS18.1, RAS22.2, UA1.6 (-)
unnamed: Q7.3 (D), RAS26.2, RAS30.2
unnamed: CAS12.1, D8.2 (K), RAS28.1
unnamed: CAS11.1, D7.2 (K), RAS27.1
unnamed: CAS10.1, D6.2 (K), RAS26.1
unnamed: CAS9.1, D2.2 (K), RAS25.1
unnamed: Q13.3 (D), RAS41.1, UA5.5 (2E), UA5.6 (3E)
unnamed: RAS33.2, UA3.8 (3Y), UA3.11 (4Y)
unnamed: Q11.3 (D), RAS35.1, UA3.6 (3E), UA3.12 (4E)
unnamed: Q10.3 (D), RAS9.1, UA3.5 (2E), UA3.13 (1E)
unnamed: Q12.3 (D), RAS36.1, UA5.12 (4E), UA5.13 (1E)
unnamed: CAP5.1, CAS1.1, RAS1.2, RAS2.1, RAS3.1
unnamed: CAS2.1, RAS6.2, UA2.2 (-)
unnamed: RAS3.2, UA2.3 (+)
unnamed: CAS1.2, CAS2.2, RAS6.1, RAS10.2, UA2.1
VCC_AMP_AUDIO: CAP6.2, CAP9.2, RAS1.1, RAS29.1, RAS30.1, RAS31.1, RAS32.1, UA1.8 (V+), UA2.8 (V+); also elsewhere on the board
VG_JFET_R1: D2.1 (A), QA1.3 (G)
VG_JFET_R2: D6.1 (A), QA2.3 (G)
VG_JFET_R3: D7.1 (A), QA4.3 (G)
VG_JFET_R4: D8.1 (A), QA3.3 (G), QA5.3 (G)

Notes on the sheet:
4.5V
2.5V
